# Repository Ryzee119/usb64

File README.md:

A project developed to use USB controllers on the Nintendo 64 console.  
Precompiled binaries can be downloaded from [Releases](https://github.com/Ryzee119/usb64/releases).  
**NOTE: This project is still in development, PRs and ideas are welcome. See todo list for ideas.**

- [x] N64 controller emulation (up to four controllers at once!).
- [x] Rumble Pak emulation.
- [x] Controller Pak emulation with four selectable banks. Technically unlimited.
- [x] Transfer Pak emulation. Put Gameboy ROMS on an SD Card!
- [x] N64 mouse emulation. Use a USB Mouse!
- [x] N64 Randnet emulation. Use a USB keyboard!
- [x] Configurable deadzones and sensitivity from the N64 Console.
- [x] True dual analog sticks with GoldenEye and Perfect Dark.
- [x] SD card driver with FATFS support for storage/backup of Gameboy ROMS, controller paks etc.
- [x] A single hardwired controller interface for ultimate hacking.
- [x] Optional TFT LCD Support.

## Todo
- [ ] Raspberry Pi interface or equivalent for all other USB controllers.
- [ ] More inbuilt USB controller drivers. (PS3, Aftermarket Xbox One, OG Xbox, improved Generic HID).
- [ ] USB Bluetooth stack.
- [ ] Mouse/Keyboard input for controllers.
- [ ] Gamecube controller support.
- [ ] Better debug output (Flashing LED, SD card logging)

## Supported Controllers
- Bluetooth 8bitdo/compatible controllers via the [8BitDo Wireless USB Adapter](https://www.8bitdo.com/wireless-usb-adapter/)
- Wired 8bitdo controllers when they are started in X-input mode.
- Xbox S/X Wired
- Xbox one Wired (Genuine / PDP)
- Xbox 360 Wired
- Xbox 360 Wireless (Via PC USB Receiver)
- PS4 Wired
- A hardwired controller, use your own buttons etc.

## Controls
- Back + D-Pad = Insert Controller Pak banks 0 to 3
- Back + LB = Insert Rumblepak
- Back + RB = Insert Transferpak
- Back + Start = Select *virtual pak* (Use in-game Controller Pak managers to configure the device)
- Back + B = Switch to true dual-analog stick more for GoldenEye 007/Perfect Dark
- Back + A = Backup buffered memory to SD Card **(DO THIS BEFORE POWER OFF!)**

## Needed Parts
| Qty | Part Description | Link |
|--|--|--|
| 1 | Teensy 4.1 | https://www.pjrc.com/store/teensy41.html |
| 1 | USB Host Cable | https://www.pjrc.com/store/cable_usb_host_t36.html |
| 3 | 0.1" Pin Header | https://www.pjrc.com/store/header_24x1.html |
| 2 | 64Mbit PSRAM  SOIC-8 | https://www.pjrc.com/store/psram.html |
| 4 | N64 Controller Extensions | [AliExpress](https://www.aliexpress.com/wholesale?catId=0&SearchText=n64%20controller%20extension) |
| 1 | (Optional) ILI9341 TFT LCD Display 2.2" (320x240) | [AliExpress](https://www.aliexpress.com/wholesale?catId=0&SearchText=ili9341%20tft) |
| 1 | MicroSD Card | - |
| 1 | (Optional) Case | https://a360.co/2HPz0U0 |
| 1 | (Optional) PCB breakout board | [Kitspace](https://kitspace.org/boards/github.com/ryzee119/usb64/) |

Note: PSRAM model numbers are IPS6404L-SQ-SPN or ESP-PSRAM64H.

## Compile and Program
See [COMPILE.md](./COMPILE.md).

## Install
See [INSTALL.md](./INSTALL.md).

## How to Use
See [USAGE.md](./USAGE.md).

## License and Attribution
usb64 is shared under the [MIT license](https://github.com/Ryzee119/usb64/blob/dev/LICENSE), however this project includes code by others. Refer to the list below.
* [mpaland](https://github.com/mpaland)/**[printf](https://github.com/mpaland/printf)** shared under the [MIT License](https://github.com/mpaland/printf/blob/master/LICENSE).
* [USBHost_t36 fork](https://github.com/Ryzee119/USBHost_t36) shared under an '[MIT or MIT-like license](https://forum.pjrc.com/threads/29382-open-source-license-issues-when-using-teensy-products?p=79667&viewfull=1#post79667)'.
* [Teensy cores](https://github.com/PaulStoffregen/cores) shared under an '[MIT or MIT-like license](https://forum.pjrc.com/threads/29382-open-source-license-issues-when-using-teensy-products?p=79667&viewfull=1#post79667)'.
* [MBC emulation code](src/n64/n64_transferpak_gbcarts.c) is adapted from [Peanut-GB](https://github.com/deltabeard/Peanut-GB) shared under an MIT License.

usb64 with optional case and TFT display.

If you like my work please consider a small donation<br>
<br>

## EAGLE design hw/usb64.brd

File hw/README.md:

# Breakout PCB
* This board was designed using [Autodesk Eagle](https://www.autodesk.com/products/eagle/overview). You can edit the `.brd` and `.sch` with this program.
* You can order via KitSpace: https://kitspace.org/boards/github.com/ryzee119/usb64/.
* Rev 1 Update: Additional 100pF capacitors have been added to each data line to improve noise rejection. See https://github.com/Ryzee119/usb64/issues/42.

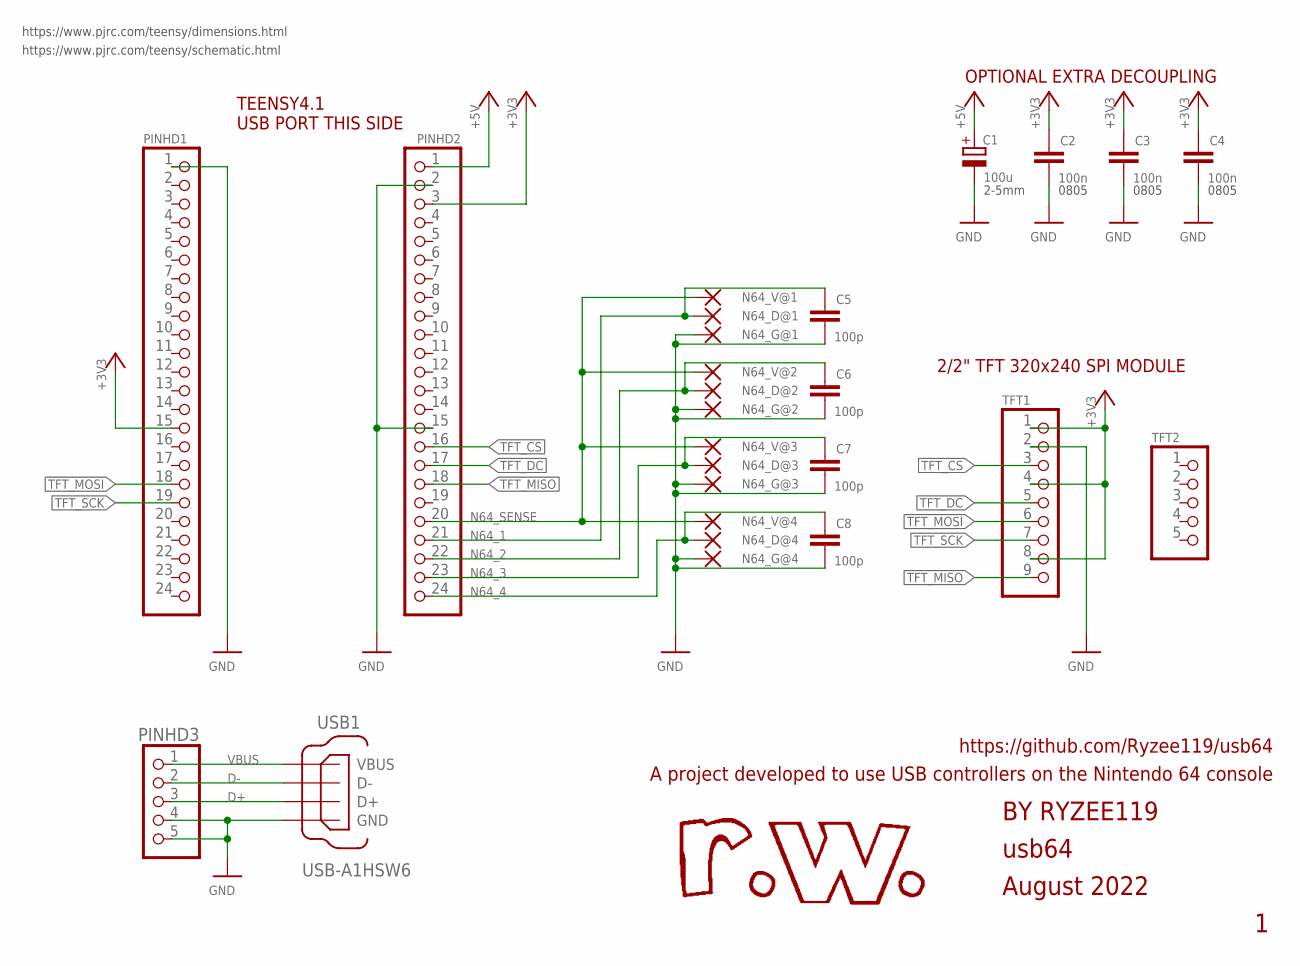
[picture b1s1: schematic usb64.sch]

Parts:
C1: 100u; E2-5
C2, C3, C4: 100n; C0805K
C5, C6, C7, C8: 100p; C0805K
N64_D@1, N64_D@2, N64_D@3, N64_D@4, N64_G@1, N64_G@2, N64_G@3, N64_G@4, N64_V@1, N64_V@2, N64_V@3, N64_V@4: SMD2; SMD1,27-2,54
PINHD1, PINHD2: PINHD-1X24; 1X24
PINHD3: PINHD-1X5; 1X05
TFT1: PINHD-1X9; 1X09
TFT2: PINHD-1X5; 1X05
USB1: USB-A1HSW6; OST_USB-A1HSW6

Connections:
+3V3: C2.1, C3.1, C4.1, PINHD1.15, PINHD2.3, TFT1.1, TFT1.4, TFT1.8
+5V: C1.+, PINHD2.1
D+: PINHD3.3, USB1.3 (D+)
D-: PINHD3.2, USB1.2 (D-)
GND: C1.-, C2.2, C3.2, C4.2, C5.2, C6.2, C7.2, C8.2, N64_G@1.1, N64_G@2.1, N64_G@3.1, N64_G@4.1, PINHD1.1, PINHD2.2, PINHD2.15, PINHD3.4, PINHD3.5, TFT1.2, USB1.4 (GND)
N64_1: C5.1, N64_D@1.1, PINHD2.21
N64_2: C6.1, N64_D@2.1, PINHD2.22
N64_3: C7.1, N64_D@3.1, PINHD2.23
N64_4: C8.1, N64_D@4.1, PINHD2.24
N64_SENSE: N64_V@1.1, N64_V@2.1, N64_V@3.1, N64_V@4.1, PINHD2.20
TFT_CS: PINHD2.16, TFT1.3
TFT_DC: PINHD2.17, TFT1.5
TFT_MISO: PINHD2.18, TFT1.9
TFT_MOSI: PINHD1.18, TFT1.6
TFT_SCK: PINHD1.19, TFT1.7
VBUS: PINHD3.1, USB1.1 (VBUS)

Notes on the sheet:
usb64
August 2022
BY RYZEE119
A project developed to use USB controllers on the Nintendo 64 console
https://github.com/Ryzee119/usb64
TEENSY4.1 USB PORT THIS SIDE
OPTIONAL EXTRA DECOUPLING
2/2" TFT 320x240 SPI MODULE
0805
2-5mm
https://www.pjrc.com/teensy/dimensions.html
https://www.pjrc.com/teensy/schematic.html

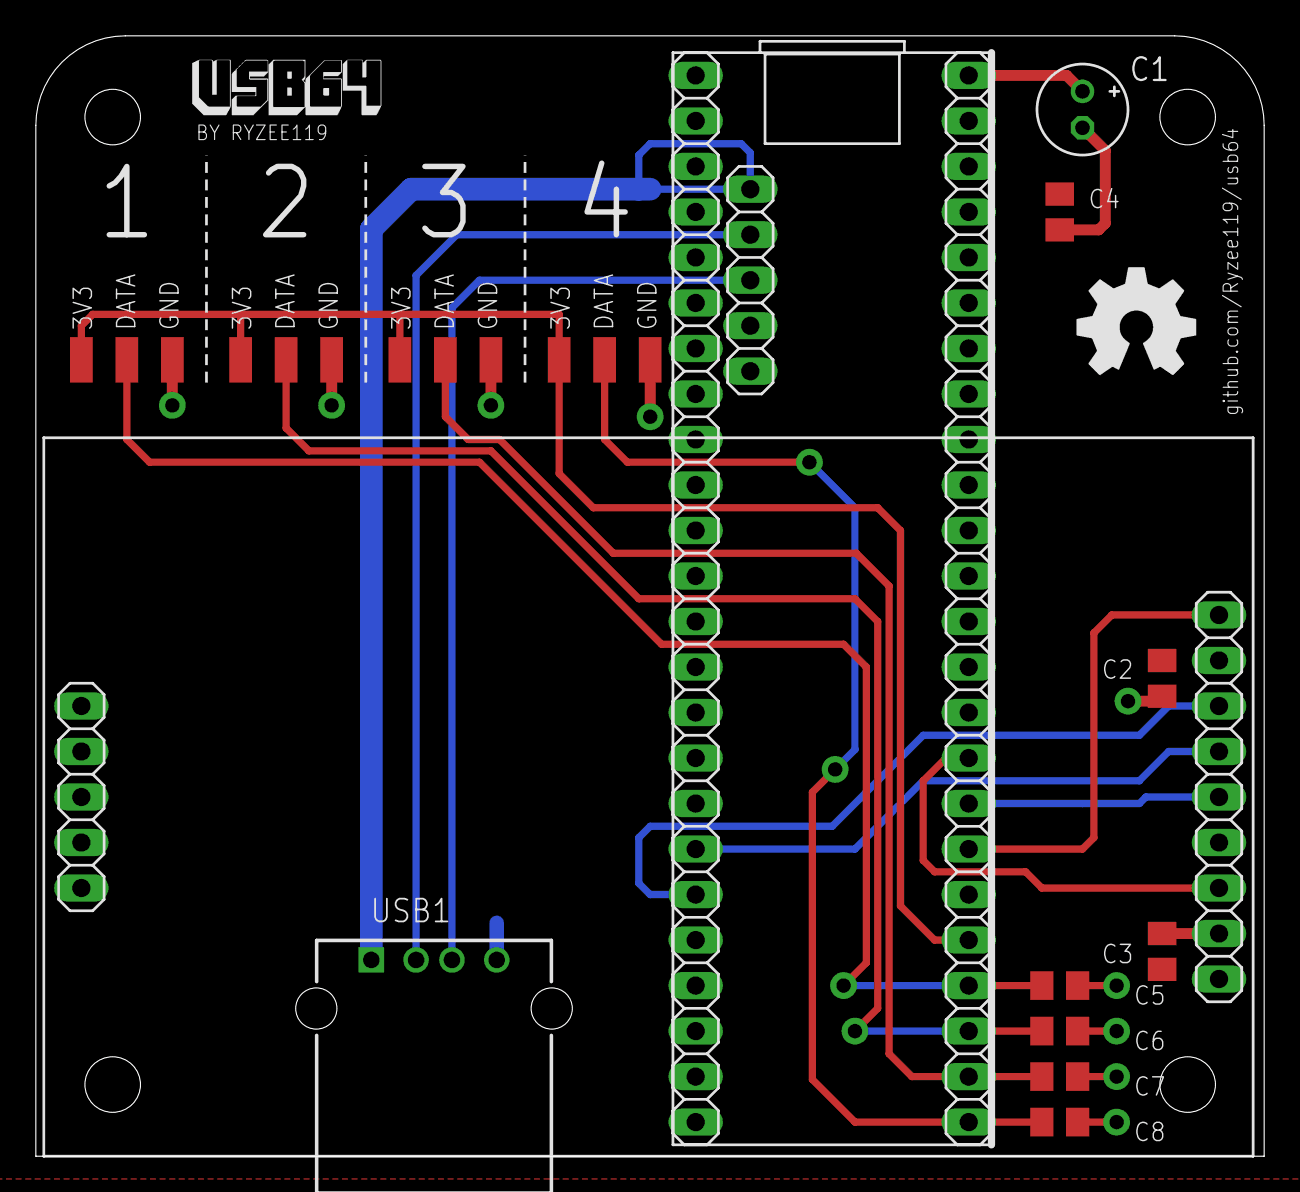
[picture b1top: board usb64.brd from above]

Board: 2 copper layers, 68.6 x 62.5 mm, 26 parts (0 on the bottom side), 16 nets.

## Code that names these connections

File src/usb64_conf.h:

// Copyright 2020, Ryan Wendland, usb64
// SPDX-License-Identifier: MIT

#ifndef _USB64_CONF_h
#define _USB64_CONF_h

/* DEBUGGING OUTPUT - WARNING SOME OF THESE MAY BREAK TIMING AND CAUSE ISSUES
   USE ONLY FOR DEBUGGING */
#define serial_port Serial1
#define DEBUG_STATUS 1  //General information
#define DEBUG_N64 0     //For debugging N64 low level info
#define DEBUG_TPAK 0    //For debugging N64 TPAK low level info. It's complex so has its own flag
#define DEBUG_USBHOST 0 //For debugging the USB Host Stack
#define DEBUG_FATFS 0   //For debugging the FATFS io
#define DEBUG_MEMORY 0  //For debugging the memory allocator in external RAM.
#define DEBUG_ERROR 1   //For showing critical errors

/* USB HOST STACK */
#define ENABLE_USB_HUB 1

/* N64 LIB */
#define MAX_CONTROLLERS 4             //Max is 4
#define MAX_MICE 4                    //0 to disable N64 mouse support. Must be <= MAX_CONTROLLERS
#define MAX_KB 4                      //0 to disable N64 randnet keyboard support. Must be <= MAX_CONTROLLERS
#define MAX_GBROMS 10                 //ROMS over this will just get ignored
#define ENABLE_I2C_CONTROLLERS 0      //Received button presses over I2C, useful for integrating with a rasp pi etc.
#define ENABLE_HARDWIRED_CONTROLLER 1 //Ability to hardware a N64 controller into the usb64.
#define PERI_CHANGE_TIME 750          //Milliseconds to simulate a peripheral changing time. Needed for some games.

/* PIN MAPPING */
#define N64_CONSOLE_SENSE 37
#define N64_CONTROLLER_1_PIN 36
#define N64_CONTROLLER_2_PIN 35
#define N64_CONTROLLER_3_PIN 34
#define N64_CONTROLLER_4_PIN 33
#define N64_FRAME 23 //Pulses high each time N64 console requests input. Presumably related to frames.
#define USER_LED_PIN 13

//Hardwired interface. All digital inputs are pulled up, active low.
#define HW_A 2
#define HW_B 3
#define HW_CU 4
#define HW_CD 5
#define HW_CL 6
#define HW_CR 7
#define HW_DU 8
#define HW_DD 9
#define HW_DL 10
#define HW_DR 11
#define HW_START 12
#define HW_Z 28
#define HW_R 29
#define HW_L 30
#define HW_RUMBLE 31 //Output, 1 when should be rumbling
#define HW_EN 32 //Active low, pulled high
#define HW_X 24 //Analog input, 0V to VCC. VCC/2 centre
#define HW_Y 25 //Analog input, 0V to VCC. VCC/2 centre

/* FILESYSTEM */
#define MAX_FILENAME_LEN 256
#define SETTINGS_FILENAME "SETTINGS.DAT"
#define GAMEBOY_SAVE_EXT ".SAV" //ROMFILENAME.SAV
#define MEMPAK_SAVE_EXT ".MPK" //MEMPAKXX.MPK

/* FIRMWARE DEFAULTS (CONFIGURABLE DURING USE) */
#define DEFAULT_SENSITIVITY 2  //0 to 4 (0 = low sensitivity, 4 = max)
#define DEFAULT_DEADZONE 2     //0 to 4 (0 = no deadzone correction, 4 = max (40%))
#define DEFAULT_SNAP 1         //0 or 1 (0 = will output raw analog stick angle, 1 will snap to 45deg angles)
#define DEFAULT_OCTA_CORRECT 1 //0 or 1 (Will correct the circular analog stuck shape to N64 octagonal)

/* FIRMWARE DEFAULTS (NOT CONFIGURABLE DURING USE) */
#define SNAP_RANGE 5           //+/- what angle range will snap. 5 will snap to 45 degree if between 40 and 50 degrees.
#define MOUSE_SENSITIVITY 2.0f //Just what felt right to me with my mouse.
#define MAG_AT_45DEG 1.1f      //Octagonal shape has a larger magnitude at the 45degree points. 1.1 times larger seems about right

/* TFT DISPLAY */
#define ENABLE_TFT_DISPLAY 1
#define TFT_ROTATION 1 //0-3
#define TFT_DC 40
#define TFT_CS 41
#define TFT_MOSI 26
#define TFT_SCK 27
#define TFT_MISO 39
#define TFT_RST 255


/* DEBUG PRINTERS */
#include "printf.h"
#define debug_print_status(fmt, ...)     do { if (DEBUG_STATUS)  printf(fmt, ##__VA_ARGS__); } while (0)
#define debug_print_n64(fmt, ...)        do { if (DEBUG_N64)     printf(fmt, ##__VA_ARGS__); } while (0)
#define debug_print_tpak(fmt, ...)       do { if (DEBUG_TPAK)    printf(fmt, ##__VA_ARGS__); } while (0)
#define debug_print_usbhost(fmt, ...)    do { if (DEBUG_USBHOST) printf(fmt, ##__VA_ARGS__); } while (0)
#define debug_print_fatfs(fmt, ...)      do { if (DEBUG_FATFS)   printf(fmt, ##__VA_ARGS__); } while (0)
#define debug_print_memory(fmt, ...)     do { if (DEBUG_MEMORY)  printf(fmt, ##__VA_ARGS__); } while (0)
#define debug_print_error(fmt, ...)      do { if (DEBUG_ERROR)   printf(fmt, ##__VA_ARGS__); } while (0)
#endif

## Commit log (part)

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2020-11-26 Readme: Update supported controllers
2020-11-28 hw: Add case link
2020-12-14 Main: Setup IO in early hook
2020-12-14 TFT: Add temperature readout
2020-12-14 n64: Only interrupt if n64 is on
2021-01-09 Readme: Update with new build image
2021-01-19 Platformio: Build to specific teensyduino verison
2021-01-20 Platformio: Build to specific teensyduino verision
2021-01-31 breakout
2021-01-31 Install: Add breakout PCB
2021-02-09 BOM: Clarify TFT size
2021-04-29 Readme: Update todo list
2021-04-29 Usage: Fix some typos
2021-05-02 Readme: Case and PCB are optional
2021-05-08 BOM: Pin header should be single row
2021-06-14 Build: Allow compilation for Teensy36
2021-07-21 Input: Use fixed input objects
2021-07-22 Input: Add Randnet keyboard emulation
2021-07-22 n64: Use timer from n64 struct
2021-07-22 usb64: Refactoring and cleanup
2021-07-22 Input: Add moree hub handlers
2021-07-22 n64: Add randnet debug prints
2021-07-22 USBH: Update submodule to 53fad12
2021-07-22 Input: Fix comments
2021-07-22 Input: Correctly check all input drivers
2021-07-22 Input: Fix Randnet led position and byte order
2021-07-22 Input: Make randnet LED booleans explicity, disable n64 debug
2021-07-22 Input: Fix randnet home button flag
2021-08-01 Readme: Add Randnet emulation support
2021-09-04 USBH: Update submodule to 2bf1112
2021-10-14 n64: Implementation of Toggle Analog Sticks
2021-10-14 n64: Iiplementation
2021-10-14 n64: implementation
2021-10-14 n64: Implentation
2021-10-26 PlatformIO: Bring up to latest teensy core
2021-10-26 Main: Make all main code cpp files
2021-10-26 Memory: Refactor defines
2021-10-26 FileIO: Remove FATFS and use SD lib
2021-10-26 N64: Fix pointer arithmetic warning
2021-10-26 Memory: Remove tinyalloc and replace with inbuilt functions
2021-10-26 N64: Reduce interrupt overhead
2021-10-26 N64: Move vars to controller struct
2021-10-27 Main: Re-add pin setup early hook
2021-10-27 FileIO: Remove uneeded variables
2021-10-28 Input: Set xinput led based on index
2021-10-28 N64: Refactor function names
2021-10-28 USBH: Update submodule to 637c4cb
2021-10-29 N64: Rework clock counter
2021-10-29 N64: Remove peri address from struct
2021-10-29 N64: Refactor N64 controller types
2021-10-29 N64: Make peri type an enum, refactor struct
2021-10-29 N64: Add small delay before sending CRC
2021-10-29 Readme: Remove legacy dependencies
2021-11-22 Input: Refactor input type checks
2021-11-23 FileIO: Rework for portability
2021-11-23 Memory: Rework for portability
2021-11-23 T4: Move HAL wrapper to Teensy folder
2021-11-23 Main: Rework for portability
2021-11-24 TFT: Rework for portability. Implement GuiLite
2021-11-24 FileIO: Add status check function
2021-11-24 HAL: Update GPIO read wrapper
2021-11-24 AStick: Remove Arduino header
2021-11-24 HAL: Add global interrupt functions
2021-11-24 Memory: Remove remaining Arduino specific code
2021-11-24 N64: Remove Arduino headers
2021-11-24 usb64: Clean up includes
2021-11-24 TFT: Move TFT code to src folder
2021-11-24 usb64: Refactor folders
2021-11-29 USBH: Replace USB Stack with TinyUSB
2021-11-30 TinyUSB: Update submodule
2021-11-30 USBH: Add Teensy4 TinyUSB driver
2021-11-30 USBH: Add xinput driver
2021-11-30 Input: Rework for TinyUSB backend
2021-11-30 Main: Update for new input backend
2021-11-30 Build: Update CI for TinyUSB
2021-11-30 USBH: Disable debug output
2021-11-30 Input: Fix warnings and remove debug messages
2021-11-30 Input: Replace ASCII defines with TinyUSB
2021-11-30 FileIO: Return 0 on success
2021-11-30 HAL: Add milli tick wrapper
2021-11-30 Conf: Fix printf wrapper linkage errors
2021-11-30 usb64: Fix warnings
2021-11-30 T4: Clean up includes
2021-11-30 usb64: Add null device
2021-11-30 n64: Use my own sprintf
2021-11-30 USBH: Add HID driver stub
2021-11-30 Xinput: Format driver
2021-11-30 usb64: Rename port folders
2021-11-30 Build: build all environments
2021-11-30 HID: Use inbuilt hid header
2021-11-30 TFT: Rework and allow use with no framebuffer
2021-11-30 Null: Comment all functions for porting
2021-11-30 N64: Fix confict with stdio
2021-11-30 Remove printf submodule
2021-11-30 Build: Link lpthread for linux test build
2021-11-30 Printf: Readd with mods
2021-11-30 TFT: Dont set pointer twice
2021-11-30 Main: Dont use stdio vprintf
2021-11-30 TinyUSB: Use my own TinyUSB fork
2021-11-30 GuiLite: Suppress warnings
2021-11-30 usb64: Fix some warnings
2021-12-03 null: Add millis to HAL
2021-12-04 T4: Move usb64_conf file to port fodler
2021-12-04 Main: Loop properly when not using Arduino
2021-12-04 TFT: Store font on ext flash
2021-12-04 Input: Store randnet map on ext flash
2021-12-04 N64: Store constant virtual mempak on ext flash
2021-12-06 Main: Assert rumble pin for HW controller
2021-12-06 TFT: Refactor TFT background colour def
2021-12-06 Ports: Add FLASHMEM define
2021-12-06 usb64: Make init functions execute from flash where possible
2021-12-06 N64: Bracket calc to prevent overflow
2021-12-07 usb64: Refactor GPIO for better portability
2021-12-07 null: Update backend for GPIO refactor
2021-12-07 t4: Update backend for GPIO refactor
2021-12-11 TFT: Reset update flag after draw
2021-12-11 TFT: Update on usb connection
2021-12-14 TFT: Move log generation to flush
2021-12-14 usb64: Rework includes and port configuration (again)
2021-12-15 TFT: Flag update after device disconncet
2021-12-15 TFT: Check malloc before use
2021-12-15 N64: Make CRC function weak
2021-12-16 TFT: Use memory malloc function
2021-12-16 Null: Add malloc wrappers
2021-12-16 T4: Add malloc wrappers
2021-12-16 N64: Use n64 malloc wrappers
2021-12-16 N64: Add malloc wrappers to header
2021-12-16 TinyUSBH: Update submodule
2021-12-16 usb64: Add stm32f7 port
2021-12-16 usb64: Update platformio.ini
2021-12-20 TFT: Use standard malloc for tft log, stop recursive logging
2021-12-20 tuh: Allow multiple hubs
2022-01-06 XINPUT: Dont parse callback if error
2022-01-06 STM32F7 USBH: Rework, multiport hubs work, more devices at once
2022-01-06 stm32f7: Disable USB IRQ too
2022-01-09 USBH: Increase enumeration buffer size
2022-01-09 stm32f7 usbh: Share control pipe, refactor functions
2022-01-11 Input: Correctly handle wireless 360 controllers
2022-01-12 Input: Add HID mouse input driver
2022-01-15 STM32F769i: Initial commit
2022-01-15 STM32F768i: Support USB HS port
2022-01-15 usb64: Add stm32f769i-dk environment
2022-01-15 STM32F768i: Boots now
2022-01-15 stm32f7 usbh: Force full speed mode, properly handle transfer speeds
2022-01-15 STM32F769I: Re-add custom linker
2022-01-15 STM32F769I: Fix GPIO interrupts
2022-01-15 STM32F769I: Disable USB HS interrupt for critical code
2022-01-15 STM32F769I: Clear pending interrupts before leaving
2022-01-15 Improve CI to upload dev artefacts Rename port_null to port_template to build with CI
2022-01-15 Generate hex output
2022-01-15 Update some defines, if they are truly required?!
2022-01-21 Input: Re-add RANDNET emulation
2022-01-21 STM32F769I: Use uart1 VCP for debugging over USB
2022-01-21 N64: Add ED64 game identifier packet
2022-01-21 STM32: Remove main.h header
2022-01-21 TFT: Print current game name on TFT
2022-01-21 STM32F7: Move common bsp port code to folder
2022-01-21 STM32F789I: Reduce SD speed
2022-01-21 TFT: Scale output on large LCDs
2022-01-26 STM32FXX: Add builds to CI
2022-01-27 Rename mempak to cpak
2022-01-27 N64 :Refactor mempak title to cpak
2022-01-28 N64 :Refactor gameid detection
2022-01-28 N64: Rename n64_mempak files
2022-01-28 TFT: Improve ROM detection
2022-01-29 N64: Improve Flashcart Detection
2022-08-08 Update submodules
2022-08-08 hw: Add 100pF filtering capacitors
2022-09-20 Install platform io wheel
2022-09-20 Update platformio.ini
    Replace deprecated `src_filter` with `build_src_filter`
2022-09-20 Update platformio.ini
    Update global filter
2022-09-20 Update platformio.ini
    Correct build_flags
2022-09-20 Update platformio.ini
    Revert change
2022-09-20 Build: Fix deprecation warnings for platformio.ini
2022-09-20 Input: Add Xbox Duke mapping
2022-09-20 TFT: Use lvgl instead of guilite
2022-09-20 Input: Add xinput lib
2022-09-21 Update build.yml
    Install wheel before platformio
2022-09-21 Build: Reorder dependancy install
    Install wheel before platformio
2022-10-26 Input: Support additional USB Hub
2024-09-14 ILI9341: Update Submodule
2024-09-14 pio: Update to teensy platform 5.0

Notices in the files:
README.md:
License: MIT
